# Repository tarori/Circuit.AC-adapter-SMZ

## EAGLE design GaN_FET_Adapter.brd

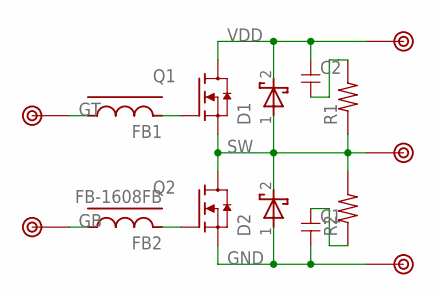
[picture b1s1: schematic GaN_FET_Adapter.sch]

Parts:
C1, C2: C-3225-2; 3225-2
D1, D2: SBD-1A2; SOD123
FB1, FB2: FB-1608FB; 1608-FB
Q1, Q2: NMOS-GAN; PQFN8X8
R1, R2: R-2012-2; 2012-2
TP1, TP2, TP3, TP4, TP5: TESTPIN-MID

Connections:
GB: FB2.1, TP4.1
GND: C1.2, D2.1 (A), Q2.S, TP3.1
GT: FB1.1, TP5.1
unnamed: C2.2, R1.2
unnamed: C1.1, R2.1
unnamed: FB2.2, Q2.G
unnamed: FB1.2, Q1.G
SW: D1.1 (A), D2.2 (K), Q1.S, Q2.D, R1.1, R2.2, TP2.1
VDD: C2.1, D1.2 (K), Q1.D, TP1.1

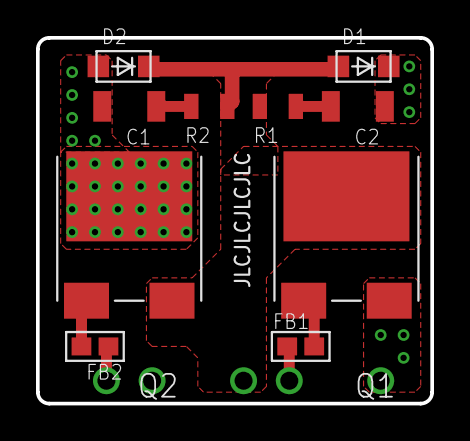
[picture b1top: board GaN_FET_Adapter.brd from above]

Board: 2 copper layers, 21.9 x 20.3 mm, 15 parts (0 on the bottom side), 9 nets.

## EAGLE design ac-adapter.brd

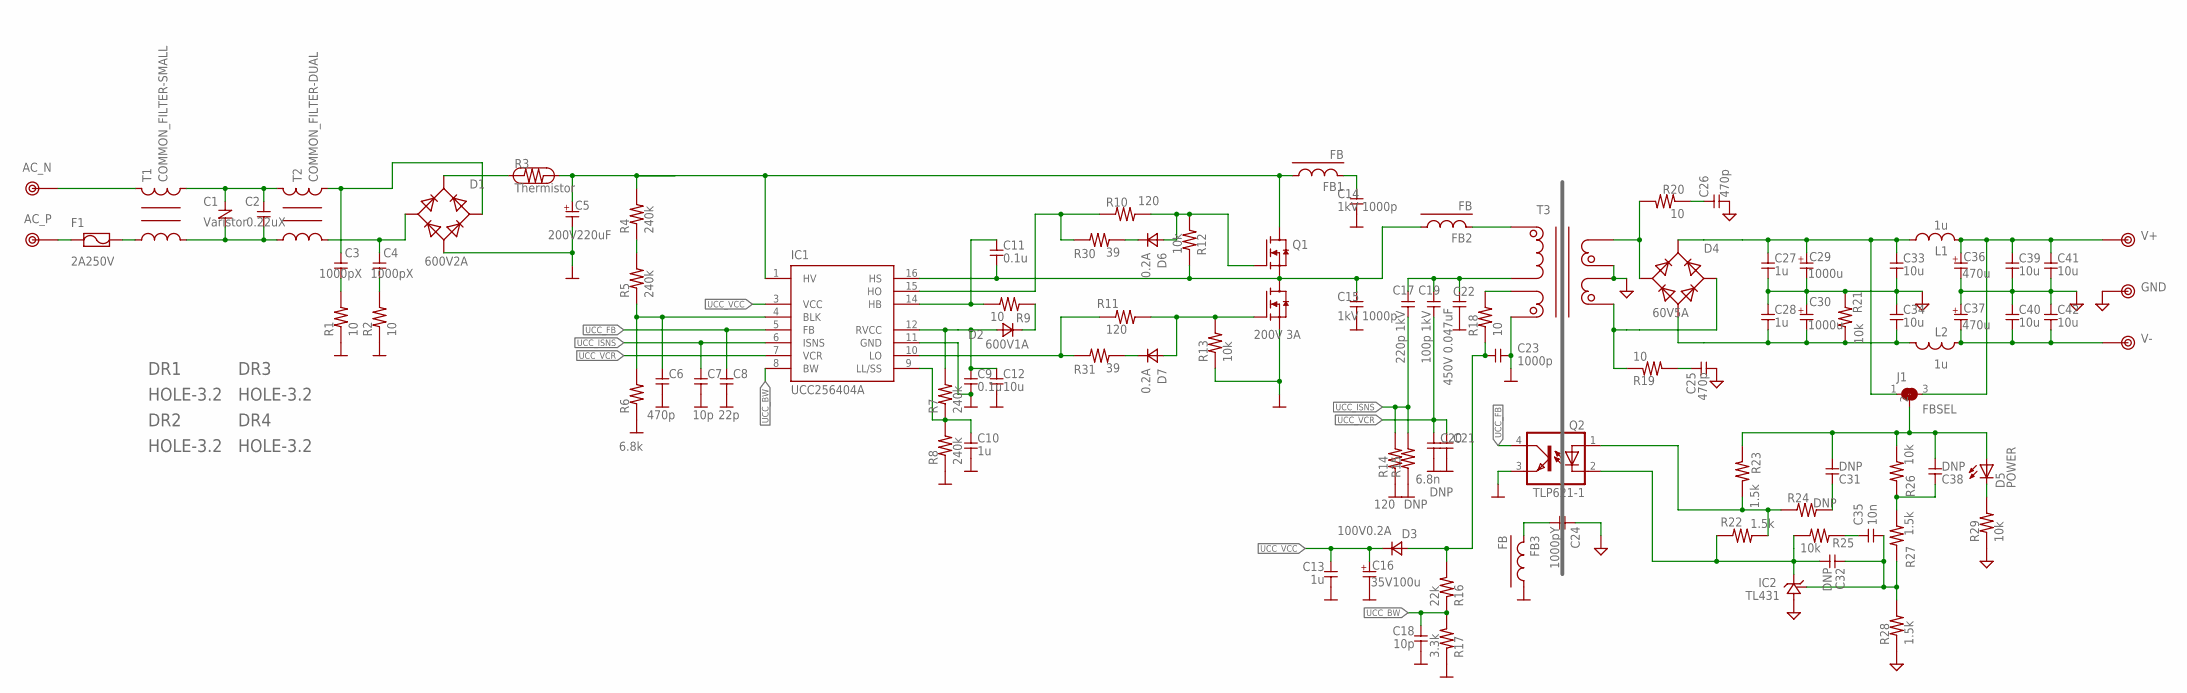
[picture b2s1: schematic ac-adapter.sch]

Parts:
C1: Varistor; V050
C2: 0.22uX; X-CAPACITER
C3, C4: 1000pX; 3216
C5: 200V220uF; E5-16A3
C6, C25, C26: 470p; 1608
C7, C18: 10p; 1608
C8: 22p; 1608
C9, C11: 0.1u; 1608
C10, C13: 1u; 1608
C12: 10u; 2012
C14, C15: 1kV 1000p; 3225
C16: 35V100u; E2,5-8
C17: 220p 1kV; 3225
C19: 100p 1kV; 3225
C20: 6.8n; 1608
C21, C31, C32, C38: DNP; 1608
C22: 450V 0.047uF; C125
C23: 1000p; 1608
C24: 1000pY; Y-CAPACITER
C27, C28: 1u; 2012-2
C29, C30: 1000u; E5-13
C33, C34, C39, C40: 10u; 3225-3
C35: 10n; 1608
C36, C37: 470u; E5-10
C41, C42: 10u; 4532-2
D1: 600V2A; GBU8A
D2: 600V1A; SOD123
D3: 100V0.2A; SOD123
D4: 60V5A; RBA-406
D5: POWER; D1608
D6, D7: 0.2A; SOD123
DR1, DR2, DR3, DR4: HOLE-3.2; HOLE_3.2
F1: 2A250V; FUSE-5
FB1, FB3: FB; 2012-FB
FB2: FB; 3216-J
IC1: UCC256404A; SO16-LACK3-13
IC2: TL431; TO-92
J1: FBSEL; 2012-3-J
L1, L2: 1u; L5-7,5
Q1: 200V 3A; NMOS-FET_HALF
Q2: TLP621-1; DIL04
R1, R2, R18, R19, R20: 10; 2012
R3: Thermistor; THERMISTOR090
R4, R5, R7, R8: 240k; 1608
R6: 6.8k; 1608
R9: 10; 1608
R10, R11, R14: 120; 1608
R12, R13, R21, R25, R26, R29: 10k; 1608
R15, R24: DNP; 1608
R16: 22k; 1608
R17: 3.3k; 1608
R22, R23, R27, R28: 1.5k; 1608
R30, R31: 39; 1608
T1: COMMON_FILTER-SMALL; COMMON_FILTER__SMALL
T2: COMMON_FILTER-DUAL; SU10VFC-DUAL
T3: TRANSFORMAER_FLYBACK-ETD34; BETD34LLC
TP1: AC_N; TESTPIN-LARGE
TP2: AC_P; TESTPIN-LARGE
TP3: V+; TESTPIN-LARGE
TP4: V-; TESTPIN-LARGE
TP5: GND; TESTPIN-LARGE

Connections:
GND: C24.1, C25.2, C26.2, C27.2, C28.1, C29.- (2), C30.+ (1), C33.2, C34.1, C36.- (2), C37.+ (1), C39.2, C40.1, C41.2, C42.1, IC2.2 (GND), R21.1, R28.1, R29.1, T3.8 (L3_P), T3.11 (L4_N), TP5.1
unnamed: T1.4, TP1.1
unnamed: D6.1 (A), Q1.GT, R10.2, R12.1
unnamed: C26.1, R20.1
unnamed: C3.1, D1.3 (AC2), T2.2, T2.6 (2)
unnamed: C4.1, D1.2 (AC1), T2.3
unnamed: C38.1, R26.1, R27.2
unnamed: D7.2 (K), R31.2
unnamed: C17.1, C19.1, C22.1, T3.3 (L1_N)
unnamed: D7.1 (A), Q1.GB, R11.1, R13.2
unnamed: C25.1, R19.2
unnamed: C3.2, R1.2
unnamed: IC1.10 (LO), R11.2, R31.1
unnamed: C14.1, FB1.2
unnamed: C11.1, IC1.14 (HB), R9.1
unnamed: D2.2 (K), R9.2
unnamed: C9.1, C12.1, D2.1 (A), IC1.12 (RVCC), R7.2
unnamed: C10.1, IC1.9 (LL/SS), R7.1, R8.2
unnamed: C6.1, IC1.4 (BLK), R5.1, R6.2
unnamed: C1.1, C2.1, T1.3, T2.1, T2.5 (1)
unnamed: IC1.15 (HO), R10.1, R30.1
unnamed: R4.1, R5.2
unnamed: R18.2, T3.6 (L2_N)
unnamed: C31.1, R24.2
unnamed: C23.1, D3.1 (A), R16.2, R18.1
unnamed: D1.1 (V+), R3.1
unnamed: F1.2, T1.1
unnamed: FB2.2, T3.1 (L1_P)
unnamed: C1.2, C2.2, T1.2, T2.4
unnamed: C32.2, IC2.3 (OUT), Q2.2 (C), R22.2, R25.1
unnamed: F1.1, TP2.1
unnamed: C24.2, FB3.2
unnamed: C32.1, C35.2, IC2.1 (REF), R27.1, R28.2
unnamed: C35.1, R25.2
unnamed: Q2.1 (A), R22.1, R23.2, R24.1
unnamed: D4.2 (AC1), R20.2, T3.9 (L3_N)
unnamed: D4.3 (AC2), R19.1, T3.10 (L4_P)
unnamed: D5.K, R29.2
unnamed: C4.2, R2.2
unnamed: D6.2 (K), R30.2
PGND: C5.- (2), C6.2, C7.2, C8.2, C9.2, C10.2, C12.2, C13.2, C14.2, C15.2, C16.- (2), C18.2, C20.2, C21.2, C22.2, C23.2, D1.4 (V-), FB3.1, IC1.11 (GND), Q1.V-, Q2.3 (EMIT), R1.1, R2.1, R6.1, R8.1, R13.1, R14.1, R15.1, R17.1, T3.5 (L2_P)
SW: C11.2, C15.1, FB2.1, IC1.16 (HS), Q1.SW, R12.2
UCC_BW: C18.1, IC1.8 (BW), R16.1, R17.2
UCC_FB: C8.1, IC1.5 (FB), Q2.4 (COL)
UCC_ISNS: C7.1, C17.2, IC1.6 (ISNS), R14.2, R15.2
UCC_VCC: C13.1, C16.+ (1), D3.2 (K), IC1.3 (VCC)
UCC_VCR: C19.2, C20.1, C21.1, IC1.7 (VCR)
V+: C27.1, C29.+ (1), C33.1, D4.1 (V+), J1.1, L1.2 (1)
V+FB: C31.2, C38.2, D5.A, J1.2, R23.1, R26.2
V+FIL: C36.+ (1), C39.1, C41.1, J1.3, L1.1 (2), TP3.1
V-: C28.2, C30.- (2), C34.2, D4.4 (V-), L2.2 (1), R21.2
V-FIL: C37.- (2), C40.2, C42.2, L2.1 (2), TP4.1
VH: C5.+ (1), FB1.1, IC1.1 (HV), Q1.V+, R3.2, R4.2

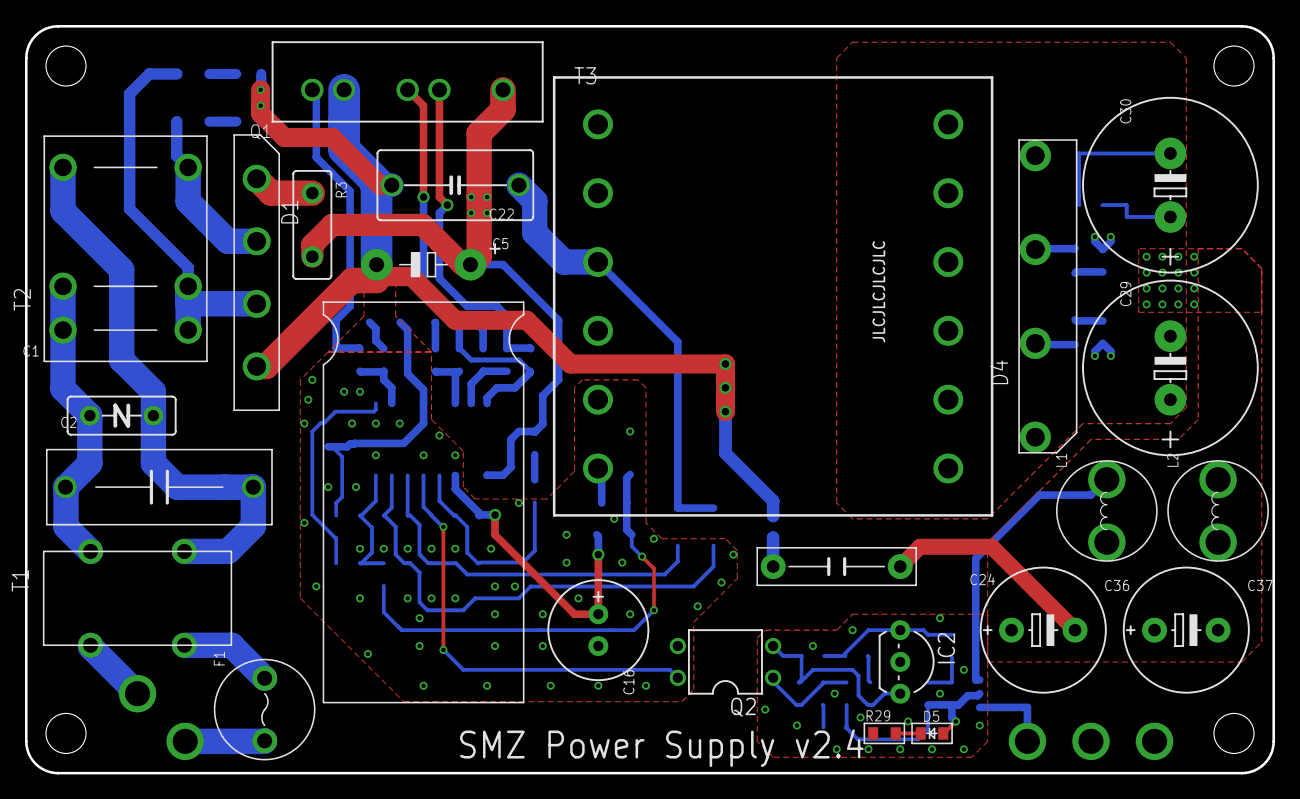
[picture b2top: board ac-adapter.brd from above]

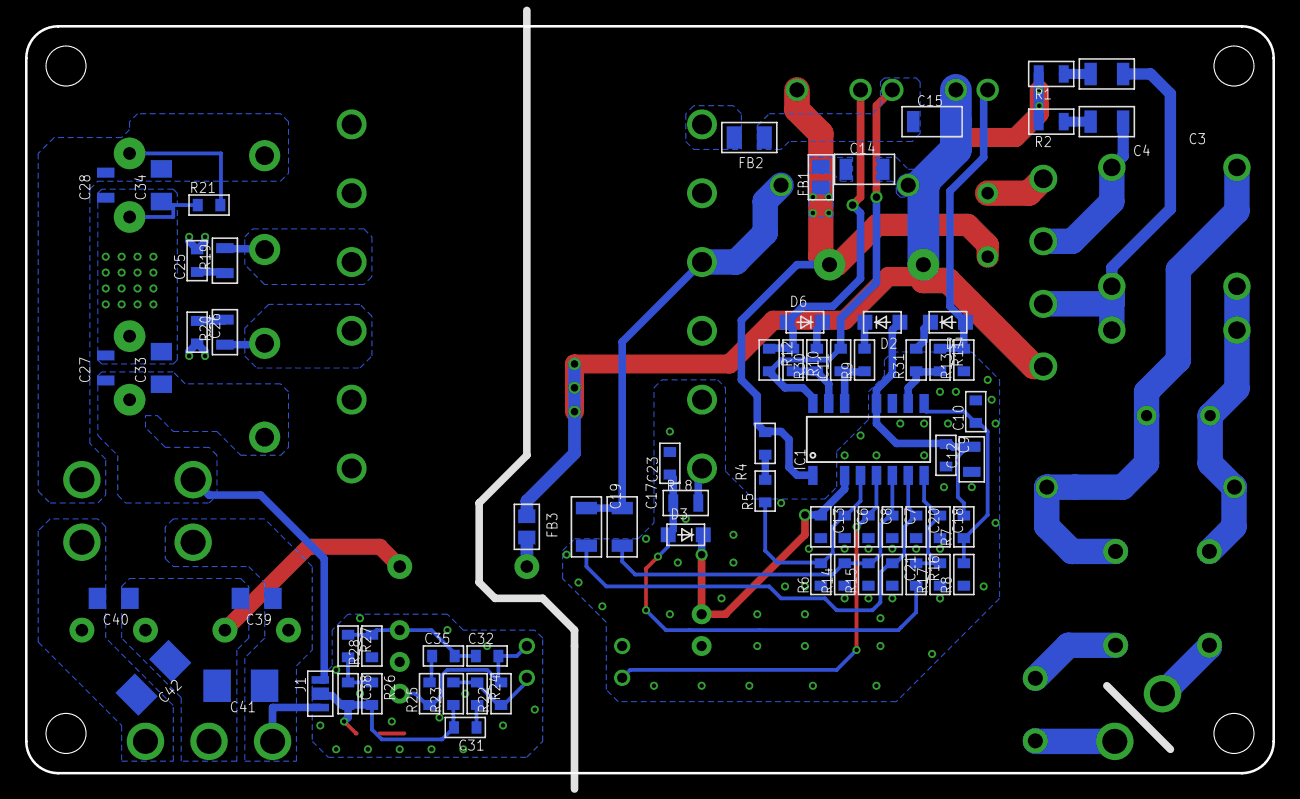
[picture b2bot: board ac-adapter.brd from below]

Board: 2 copper layers, 99.7 x 59.7 mm, 103 parts (70 on the bottom side), 53 nets.

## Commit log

2023-11-04 Ver1
2023-11-04 GaNに変更
2023-11-05 UCC256404Aに変更
2023-11-19 ver2.3 GaNとSiを共通に
2024-01-03 曲げる前
